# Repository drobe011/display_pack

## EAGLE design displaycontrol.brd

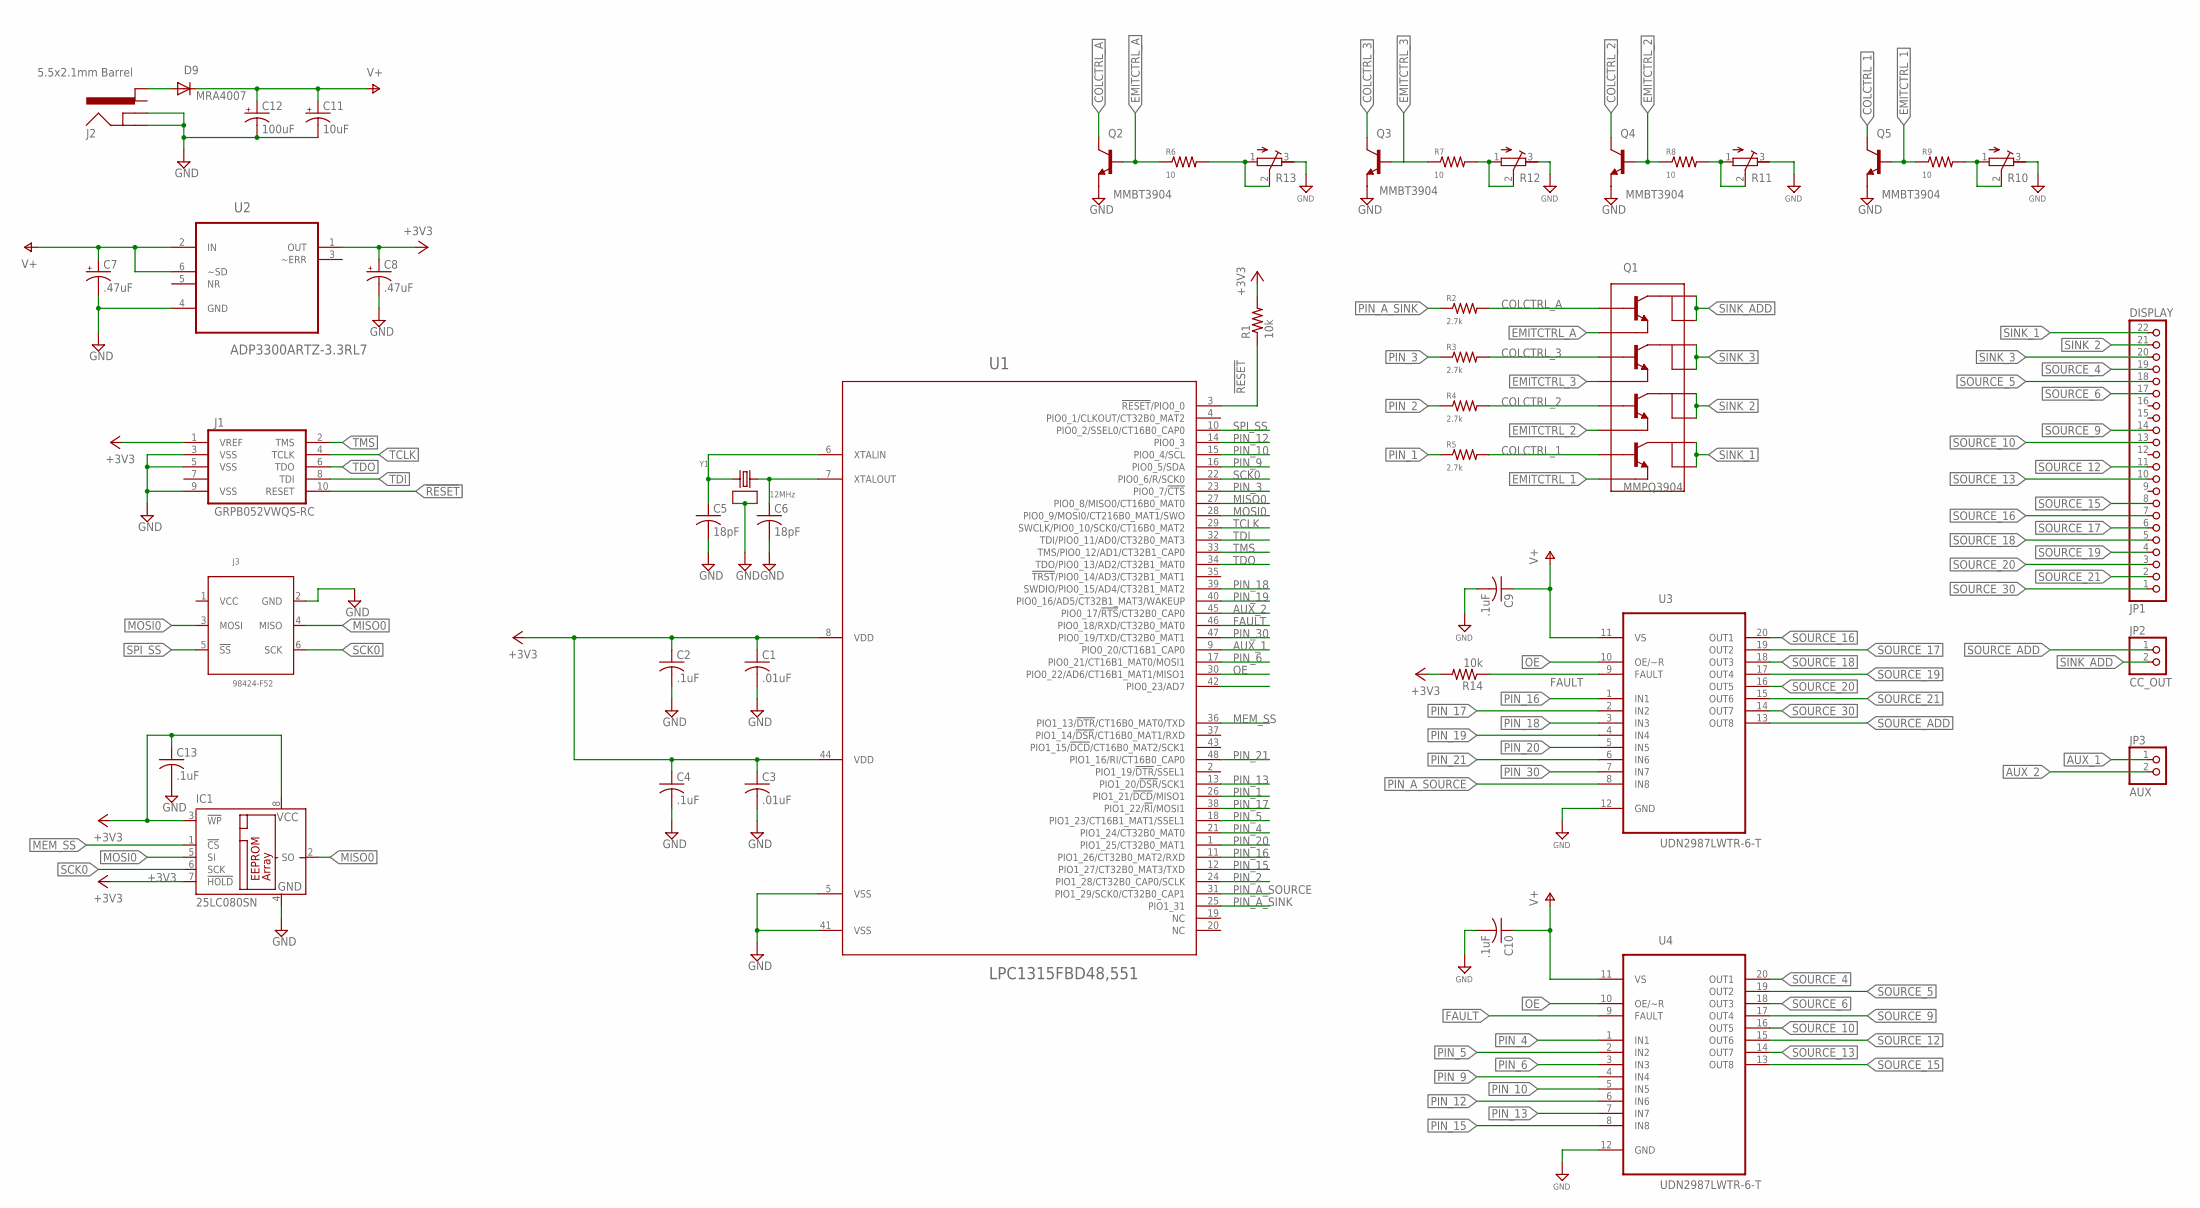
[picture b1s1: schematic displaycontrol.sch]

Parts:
C1, C3: .01uF; C0805
C2, C4, C9, C10, C13: .1uF; C0805
C5, C6: 18pF; C0805
C7, C8: .47uF; EIA3216
C11: 10uF; 153CLV-0405
C12: 100uF; 153CLV-0605
D9: MRA4007; SOD-123_MINI-SMA
IC1: 25LC080SN; SO-08
J1: GRPB052VWQS-RC
J2: 5.5x2.1mm Barrel; POWER_JACK_SMD
J3: 98424-F52; 2X3_2MM_SMD
JP1: DISPLAY; 1X22
JP2: CC_OUT; 1X02
JP3: AUX; 1X02
Q1: MMPQ3904; SO16
Q2, Q3, Q4, Q5: MMBT3904; SOT23-3
R1, R14: 10k; R0805
R2, R3, R4, R5: 2.7k; R0805
R6, R7, R8, R9: 10; R0805
R10, R11, R12, R13: R-TRIMM3214W; RTRIM3214W
U1: LPC1315FBD48,551; QFP50P900X900X160-48N
U2: ADP3300ARTZ-3.3RL7; SOT95P275X145-6N
U3, U4: UDN2987LWTR-6-T; SO20W
Y1: 12MHz; 5X3.2MM

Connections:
!RESET!: J1.10 (RESET), R1.1, U1.3 (!RESET!/PIO0_0)
+3V3: C1.1, C2.1, C3.1, C4.1, C8.A (+), C13.1, IC1.3 (!WP), IC1.7 (!HOLD), IC1.8 (VCC), J1.1 (VREF), R1.2, R14.2, U1.8 (VDD), U1.44 (VDD), U2.1 (OUT)
AUX_1: JP3.1, U1.9 (PIO0_20/CT16B1_CAP0)
AUX_2: JP3.2, U1.45 (PIO0_17/!RTS!/CT32B0_CAP0)
COLCTRL_1: Q1.9 (B4), Q5.3 (C), R5.2
COLCTRL_2: Q1.11 (B3), Q4.3 (C), R4.2
COLCTRL_3: Q1.13 (B2), Q3.3 (C), R3.2
COLCTRL_A: Q1.15 (B1), Q2.3 (C), R2.2
EMITCTRL_1: Q1.10 (E4), Q5.1 (B), R9.1
EMITCTRL_2: Q1.12 (E3), Q4.1 (B), R8.1
EMITCTRL_3: Q1.14 (E2), Q3.1 (B), R7.1
EMITCTRL_A: Q1.16 (E1), Q2.1 (B), R6.1
FAULT: R14.1, U1.46 (PIO0_18/RXD/CT32B0_MAT0), U3.9 (FAULT), U4.9 (FAULT)
GND: C1.2, C2.2, C3.2, C4.2, C5.2, C6.2, C7.C (-), C8.C (-), C9.2, C10.2, C11.-, C12.-, C13.2, IC1.4 (GND), J1.3 (VSS), J1.5 (VSS), J1.9 (VSS), J2.GND (GNDBREAK), J2.P$4 (GND), J3.2 (GND), Q2.2 (E), Q3.2 (E), Q4.2 (E), Q5.2 (E), R10.3 (A), R11.3 (A), R12.3 (A), R13.3 (A), U1.5 (VSS), U1.41 (VSS), U2.4 (GND), U3.12 (GND), U4.12 (GND), Y1.2 (GND), Y1.4 (GND)
MEM_SS: IC1.1 (!CS), U1.36 (PIO1_13/!DTR!/CT16B0_MAT0/TXD)
MISO0: IC1.2 (SO), J3.4 (MISO), U1.27 (PIO0_8/MISO0/CT16B0_MAT0)
MOSI0: IC1.5 (SI), J3.3 (MOSI), U1.28 (PIO0_9/MOSI0/CT216B0_MAT1/SWO)
unnamed: C6.1, U1.7 (XTALOUT), Y1.3 (2)
unnamed: C5.1, U1.6 (XTALIN), Y1.1
unnamed: R6.2, R13.1 (E), R13.2 (S)
unnamed: R7.2, R12.1 (E), R12.2 (S)
unnamed: R8.2, R11.1 (E), R11.2 (S)
unnamed: R9.2, R10.1 (E), R10.2 (S)
unnamed: D9.A, J2.VIN1 (PWR1)
OE: U1.30 (PIO0_22/AD6/CT16B1_MAT1/MISO1), U3.10 (OE/~R), U4.10 (OE/~R)
PIN_1: R5.1, U1.26 (PIO1_21/!DCD!/MISO1)
PIN_2: R4.1, U1.24 (PIO1_28/CT32B0_CAP0/SCLK)
PIN_3: R3.1, U1.23 (PIO0_7/!CTS!)
PIN_4: U1.21 (PIO1_24/CT32B0_MAT0), U4.1 (IN1)
PIN_5: U1.18 (PIO1_23/CT16B1_MAT1/SSEL1), U4.2 (IN2)
PIN_6: U1.17 (PIO0_21/CT16B1_MAT0/MOSI1), U4.3 (IN3)
PIN_9: U1.16 (PIO0_5/SDA), U4.4 (IN4)
PIN_10: U1.15 (PIO0_4/SCL), U4.5 (IN5)
PIN_12: U1.14 (PIO0_3), U4.6 (IN6)
PIN_13: U1.13 (PIO1_20/!DSR!/SCK1), U4.7 (IN7)
PIN_15: U1.12 (PIO1_27/CT32B0_MAT3/TXD), U4.8 (IN8)
PIN_16: U1.11 (PIO1_26/CT32B0_MAT2/RXD), U3.1 (IN1)
PIN_17: U1.38 (PIO1_22/!RI!/MOSI1), U3.2 (IN2)
PIN_18: U1.39 (SWDIO/PIO0_15/AD4/CT32B1_MAT2), U3.3 (IN3)
PIN_19: U1.40 (PIO0_16/AD5/CT32B1_MAT3/WAKEUP), U3.4 (IN4)
PIN_20: U1.1 (PIO1_25/CT32B0_MAT1), U3.5 (IN5)
PIN_21: U1.48 (PIO1_16/RI/CT16B0_CAP0), U3.6 (IN6)
PIN_30: U1.47 (PIO0_19/TXD/CT32B0_MAT1), U3.7 (IN7)
PIN_A_SINK: R2.1, U1.25 (PIO1_31)
PIN_A_SOURCE: U1.31 (PIO1_29/SCK0/CT32B0_CAP1), U3.8 (IN8)
SCK0: IC1.6 (SCK), J3.6 (SCK), U1.22 (PIO0_6/R/SCK0)
SINK_1: JP1.22, Q1.7 (C4), Q1.8 (C4)
SINK_2: JP1.21, Q1.5 (C3), Q1.6 (C3)
SINK_3: JP1.20, Q1.3 (C2), Q1.4 (C2)
SINK_ADD: JP2.2, Q1.1 (C1), Q1.2 (C1)
SOURCE_4: JP1.19, U4.20 (OUT1)
SOURCE_5: JP1.18, U4.19 (OUT2)
SOURCE_6: JP1.17, U4.18 (OUT3)
SOURCE_9: JP1.14, U4.17 (OUT4)
SOURCE_10: JP1.13, U4.16 (OUT5)
SOURCE_12: JP1.11, U4.15 (OUT6)
SOURCE_13: JP1.10, U4.14 (OUT7)
SOURCE_15: JP1.8, U4.13 (OUT8)
SOURCE_16: JP1.7, U3.20 (OUT1)
SOURCE_17: JP1.6, U3.19 (OUT2)
SOURCE_18: JP1.5, U3.18 (OUT3)
SOURCE_19: JP1.4, U3.17 (OUT4)
SOURCE_20: JP1.3, U3.16 (OUT5)
SOURCE_21: JP1.2, U3.15 (OUT6)
SOURCE_30: JP1.1, U3.14 (OUT7)
SOURCE_ADD: JP2.1, U3.13 (OUT8)
SPI_SS: J3.5 (!SS!), U1.10 (PIO0_2/SSEL0/CT16B0_CAP0)
TCLK: J1.4 (TCLK), U1.29 (SWCLK/PIO0_10/SCK0/CT16B0_MAT2)
TDI: J1.8 (TDI), U1.32 (TDI/PIO0_11/AD0/CT32B0_MAT3)
TDO: J1.6 (TDO), U1.34 (TDO/PIO0_13/AD2/CT32B1_MAT0)
TMS: J1.2 (TMS), U1.33 (TMS/PIO0_12/AD1/CT32B1_CAP0)
V+: C7.A (+), C9.1, C10.1, C11.+, C12.+, D9.C, U2.2 (IN), U2.6 (~SD), U3.11 (VS), U4.11 (VS)
VCC: J3.1 (VCC)

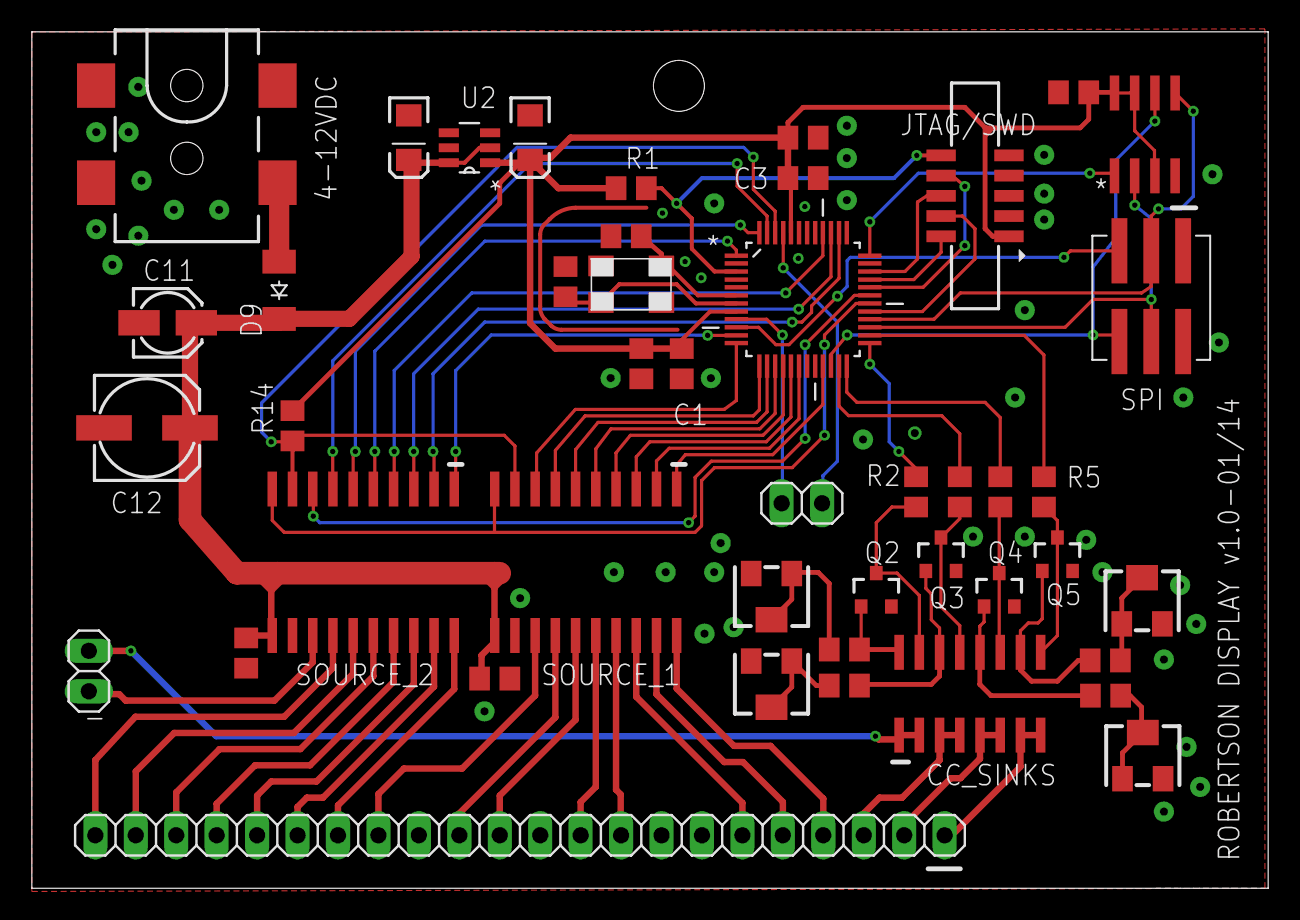
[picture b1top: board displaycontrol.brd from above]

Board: 2 copper layers, 77.6 x 53.8 mm, 45 parts (0 on the bottom side), 72 nets.

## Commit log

2014-01-03 Initial
2014-01-06 changed trans

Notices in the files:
parts and their libraries:
SparkFun-Capacitors: Licensing: CC v3.0 Share-Alike You are welcome to use this library for commercial purposes.
